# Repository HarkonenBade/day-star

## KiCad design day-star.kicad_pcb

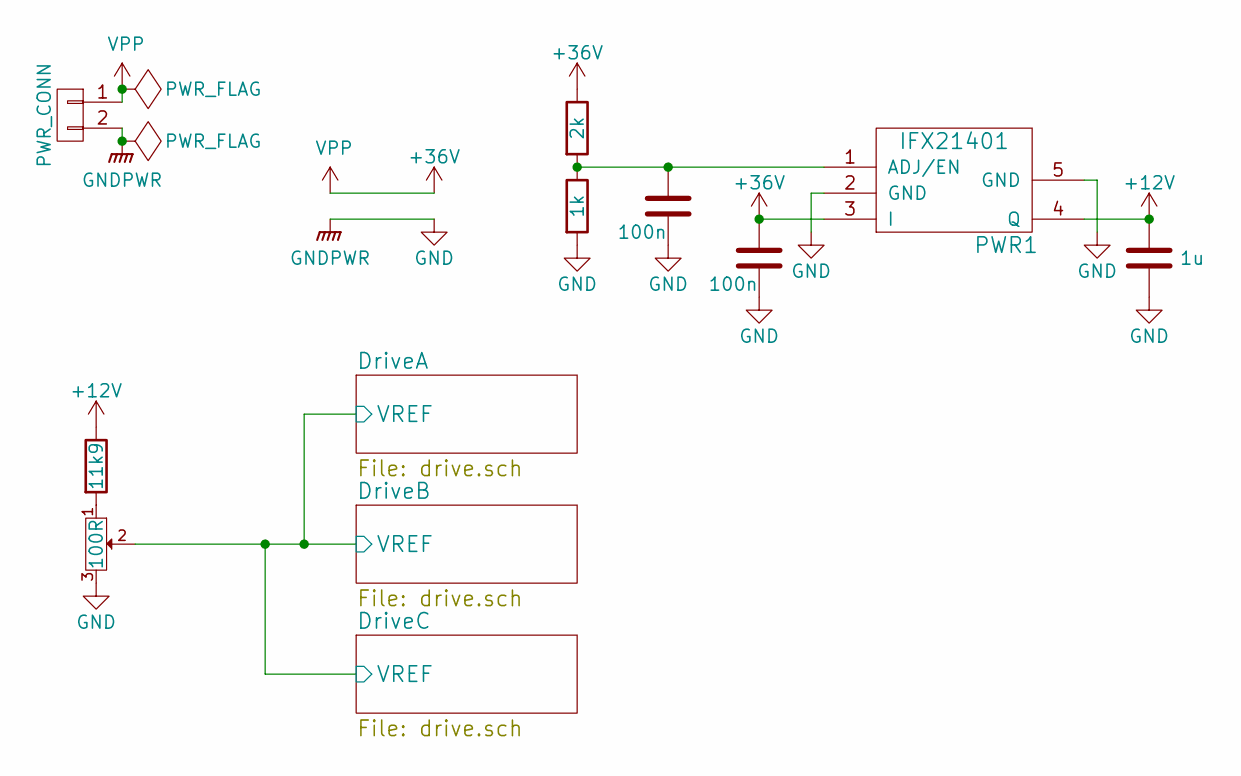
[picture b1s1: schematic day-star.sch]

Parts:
C1, C2: 100n; 0603
C3: 1u; 0603
P1: PWR_CONN; TerminalBlock_Pheonix_MKDS1.5-2pol
PWR1: IFX21401; PG-SCT595-5; Farnell 2215570
R1: 2k; 0603
R2: 1k; 0603
R3: 11k9; 0603
RV1: 100R; SIL-254P-03

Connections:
+12V: C3.1, PWR1.4 (Q), R3.1; also elsewhere on the board
+36V: C2.1, P1.1, PWR1.3 (I), R1.1; also elsewhere on the board
/DriveA/VREF: RV1.2; also elsewhere on the board
GND: C1.2, C2.2, C3.2, P1.2, PWR1.2 (GND), PWR1.5 (GND), R2.2, RV1.3; also elsewhere on the board
unnamed: C1.1, PWR1.1 (ADJ/EN), R1.2, R2.1
unnamed: R3.2, RV1.1

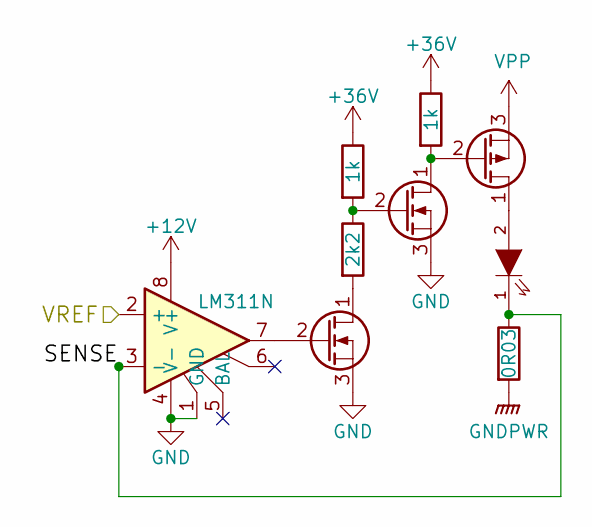
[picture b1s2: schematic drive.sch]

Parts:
D1: LED; TerminalBlock_Pheonix_MKDS1.5-2pol
Q1: Q_PMOS_DGS; TO-220_Neutral123_Horizontal_LargePads
Q2, Q3: Q_NMOS_DGS; SOT-23
R4, R5: 1k; 0603
R6: 2k2; 0603
R7: 0R03; R_2512
U1: LM311N; MSOP-8

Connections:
+12V: U1.8 (V+); also elsewhere on the board
+36V: Q1.3 (S), R4.1, R5.1; also elsewhere on the board
/DriveA/SENSE: D1.1 (K), R7.1, U1.3 (-)
/DriveA/VREF: U1.2 (+); also elsewhere on the board
GND: Q2.3 (S), Q3.3 (S), R7.2, U1.1 (GND), U1.4 (V-); also elsewhere on the board
unnamed: D1.2 (A), Q1.1 (D)
unnamed: Q1.2 (G), Q2.1 (D), R4.2
unnamed: Q2.2 (G), R5.2, R6.1
unnamed: Q3.1 (D), R6.2
unnamed: Q3.2 (G), U1.7

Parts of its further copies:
D2, D3: LED; TerminalBlock_Pheonix_MKDS1.5-2pol
Q4, Q7: Q_PMOS_DGS; TO-220_Neutral123_Horizontal_LargePads
Q5, Q6, Q8, Q9: Q_NMOS_DGS; SOT-23
R8, R9, R12, R13: 1k; 0603
R10, R14: 2k2; 0603
R11, R15: 0R03; R_2512
U2, U3: LM311N; MSOP-8

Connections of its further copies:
+12V: U2.8 (V+), U3.8 (V+); also elsewhere on the board
+36V: Q4.3 (S), Q7.3 (S), R8.1, R9.1, R12.1, R13.1; also elsewhere on the board
/DriveA/VREF: U2.2 (+), U3.2 (+); also elsewhere on the board
/DriveB/SENSE: D2.1 (K), R11.1, U2.3 (-)
/DriveC/SENSE: D3.1 (K), R15.1, U3.3 (-)
GND: Q5.3 (S), Q6.3 (S), Q8.3 (S), Q9.3 (S), R11.2, R15.2, U2.1 (GND), U2.4 (V-), U3.1 (GND), U3.4 (V-); also elsewhere on the board
unnamed: D2.2 (A), Q4.1 (D)
unnamed: D3.2 (A), Q7.1 (D)
unnamed: Q4.2 (G), Q5.1 (D), R8.2
unnamed: Q5.2 (G), R9.2, R10.1
unnamed: Q6.1 (D), R10.2
unnamed: Q6.2 (G), U2.7
unnamed: Q7.2 (G), Q8.1 (D), R12.2
unnamed: Q8.2 (G), R13.2, R14.1
unnamed: Q9.1 (D), R14.2
unnamed: Q9.2 (G), U3.7

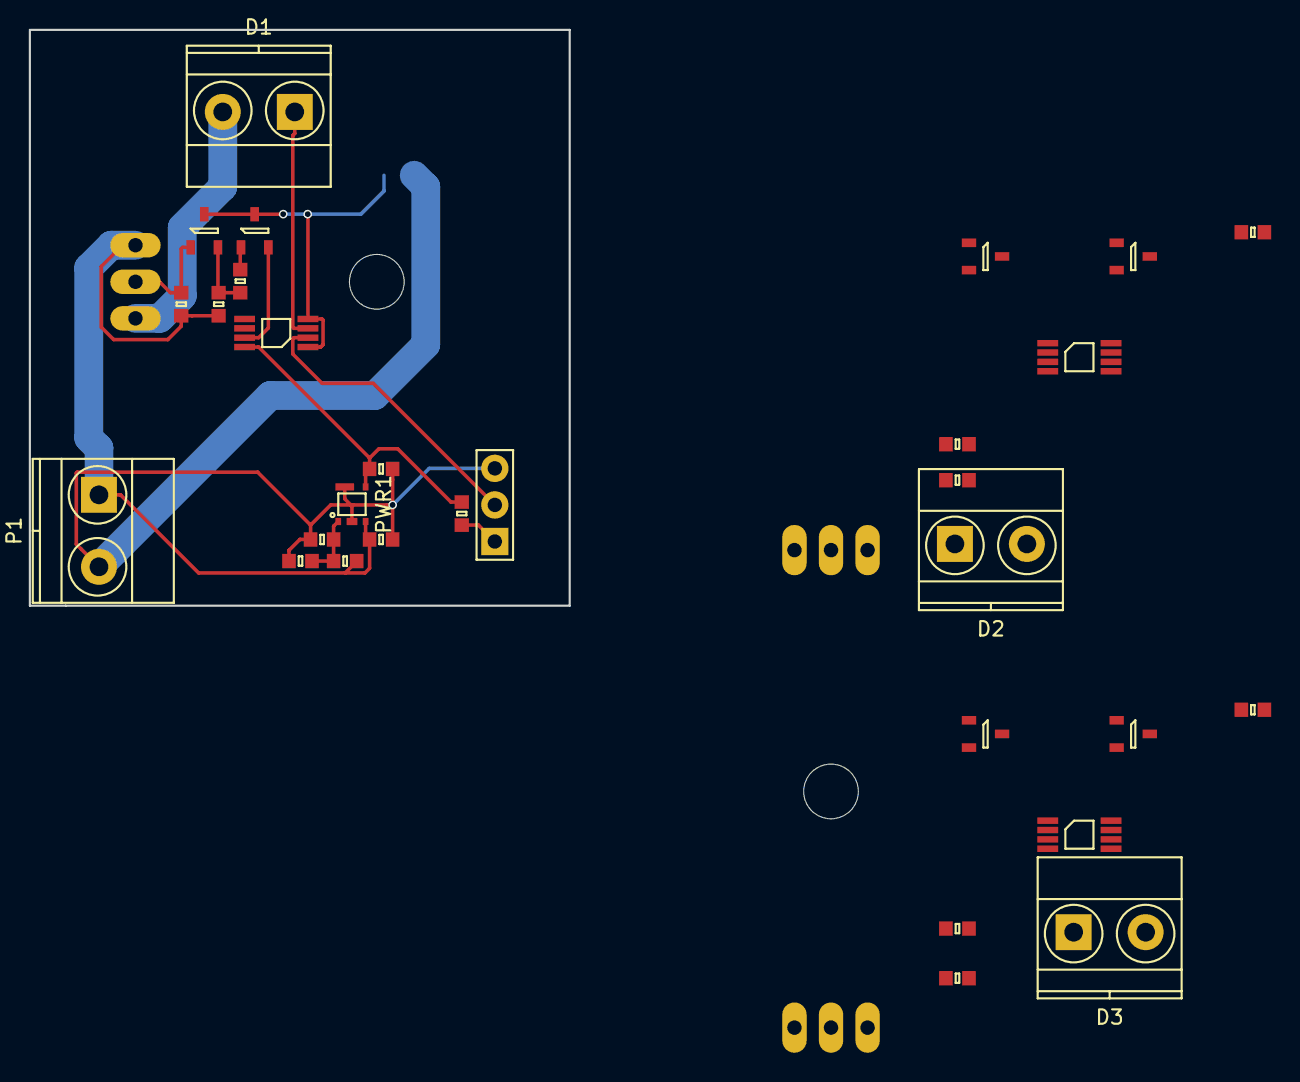
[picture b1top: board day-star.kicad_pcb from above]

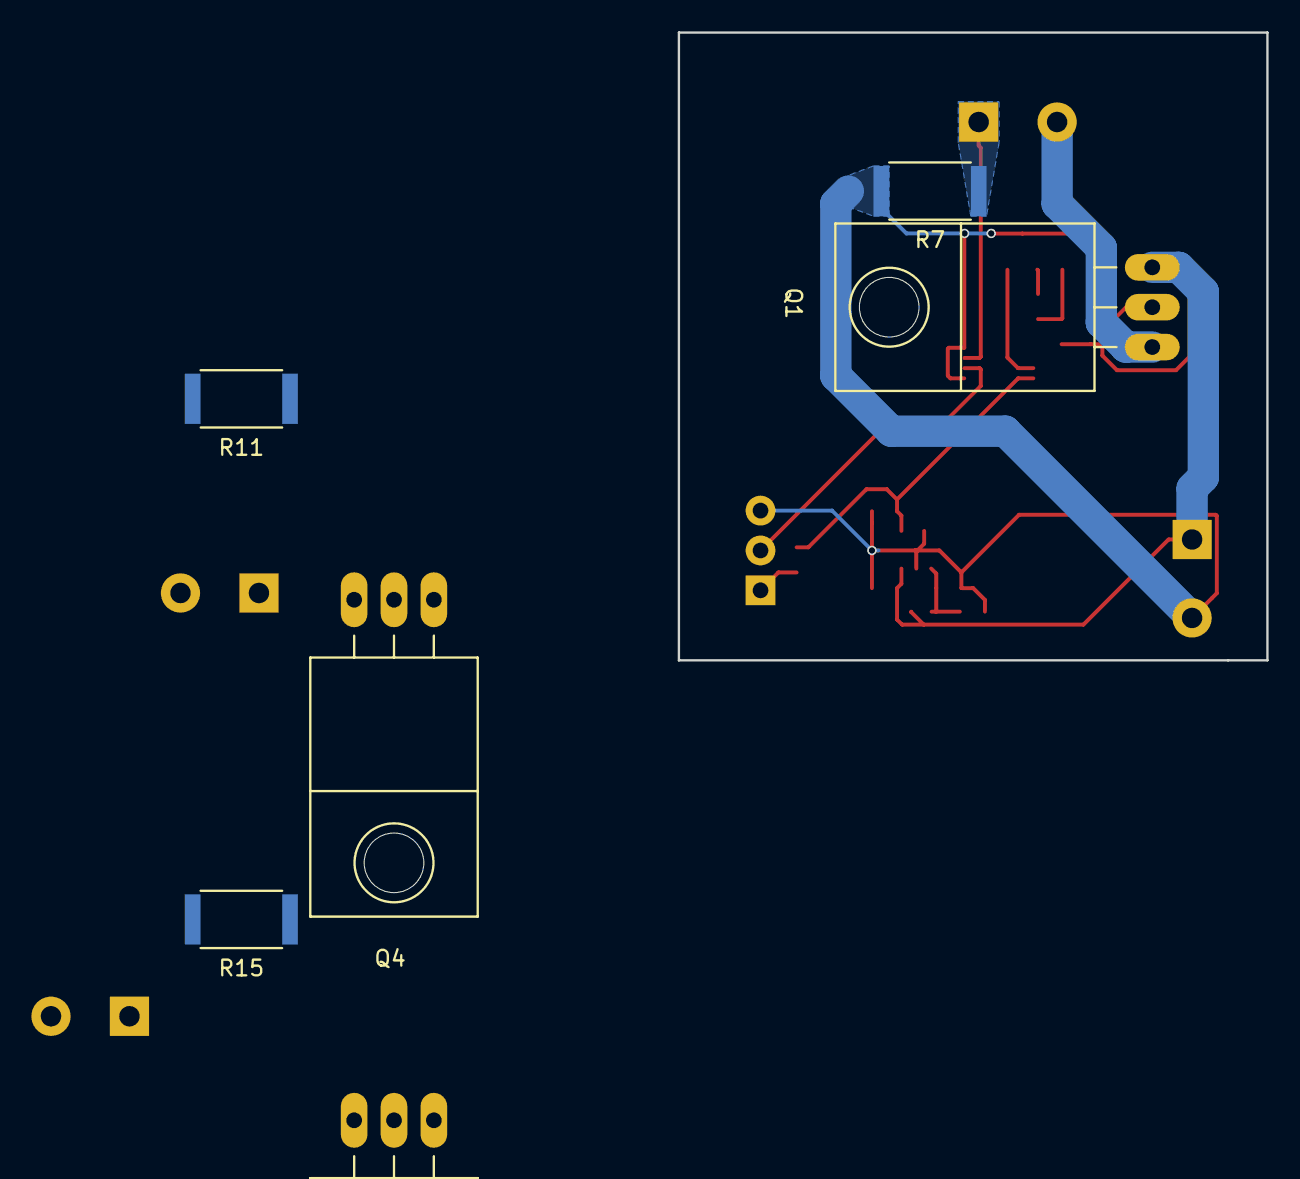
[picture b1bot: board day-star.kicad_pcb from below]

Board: 2 copper layers, 37.5 x 40.0 mm, 36 parts (6 on the bottom side), 24 nets.

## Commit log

2016-04-14 Original Schema
2016-04-14 Power pin wrangling
2016-04-14 12V regulator and proper ref voltage creation.
2016-04-15 Messing around
2016-06-28 Shiggles
2016-06-28 Continuing shiggles
2016-11-09 Update agg-kicad
2016-11-09 Tweaked bits and started setup for IC driven version
2016-11-11 More shenanigans, starting to put together power supplies
2016-11-21 More schematic wrangling
2016-12-12 Bunch of small changes
2016-12-13 Split boards, bunch of tweaks, WIP
2016-12-15 Component values for TPS
2016-12-15 More controller tweaks
